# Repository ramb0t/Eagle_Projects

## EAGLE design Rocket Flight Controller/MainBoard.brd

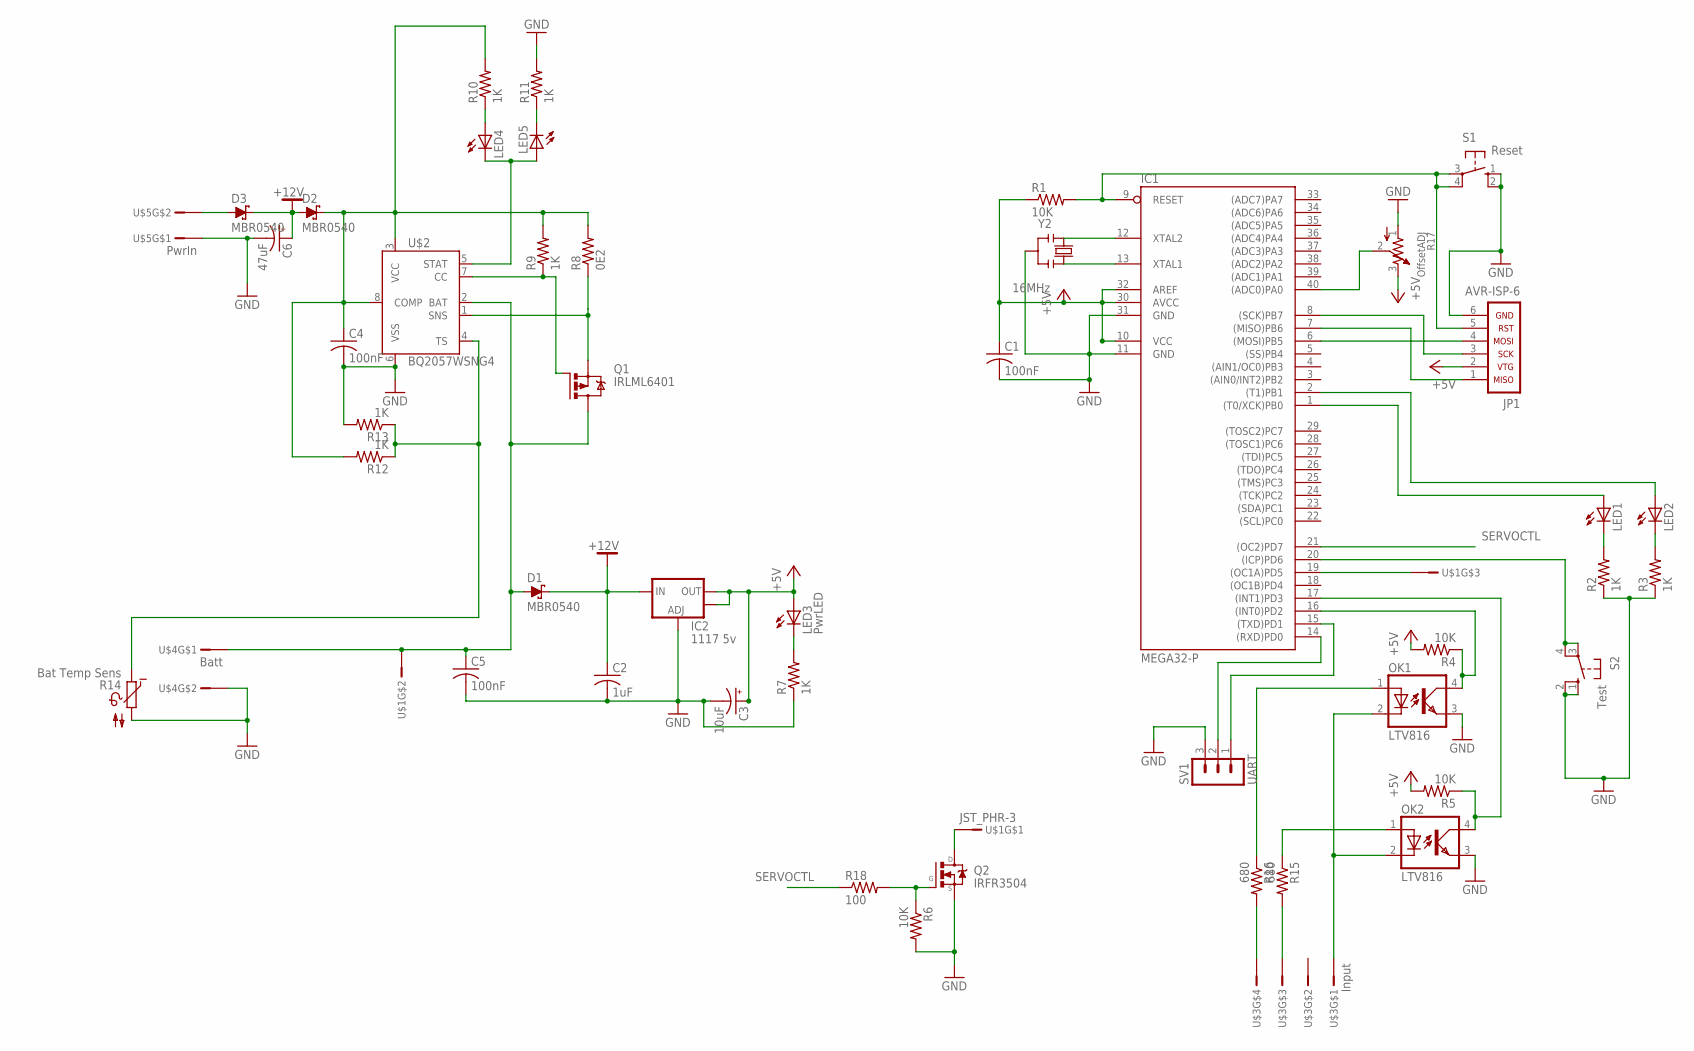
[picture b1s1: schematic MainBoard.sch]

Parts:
C1, C4, C5: 100nF; C0805K
C2: 1uF; C0805K
C3: 10uF; E2,5-7
C6: 47uF; E2,5-7
D1, D2, D3: MBR0540; SOD123
IC1: MEGA32-P; DIL40
IC2: 1117 5v; SOT223
JP1: AVR-ISP-6
LED1, LED2, LED4, LED5: LED3MM
LED3: PwrLED; LED3MM
OK1, OK2: LTV816; DIL04
Q1: IRLML6401; MICRO3
Q2: IRFR3504; DPAK
R1, R4, R5, R6: 10K; R0805
R2, R3, R7, R9, R10, R11, R12, R13: 1K; R0805
R8: 0E2; M1206
R14: Bat Temp Sens; P640
R15, R16: 680; R0805
R17: OffsetADJ; 3362P
R18: 100; R0805
S1: Reset; B3F-10XX
S2: Test; B3F-10XX
SV1: UART; MA03-1
U$1: JST_PHR-3; PHR-3
U$2: BQ2057WSNG4; D_R-PDSO-G8
U$3: Input; PHR-4
U$4: Batt; PHR-2
U$5: PwrIn; PHR-2
Y2: 16MHz; RESONATOR

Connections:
+5V: C1.1, C3.+, IC1.10 (VCC), IC1.30 (AVCC), IC1.32 (AREF), IC2.2 (OUT), IC2.4 (OUT), JP1.2, LED3.A, R1.1, R4.2, R5.2, R17.3
+12V: C2.1, C6.+, D1.C, D2.A, D3.C, IC2.3 (IN)
GND: C1.2, C2.2, C3.-, C4.2, C5.2, C6.-, IC1.11 (GND), IC1.31 (GND), IC2.1 (ADJ), JP1.6, OK1.3 (EMIT), OK2.3 (EMIT), Q2.3 (S), R2.1, R3.1, R6.2, R7.1, R11.2, R13.2, R14.2, R17.1, S1.1 (S), S1.2 (S1), S2.1 (S), S2.2 (S1), SV1.3, U$2.6 (VSS), U$4.P$2, U$5.P$1, Y2.2
unnamed: OK1.2 (C), OK2.2 (C), U$3.P$1
unnamed: IC1.9 (RESET), JP1.5, R1.2, S1.3, S1.4 (P1)
unnamed: IC1.8 ((SCK)PB7), JP1.3
unnamed: IC1.6 ((MOSI)PB5), JP1.4
unnamed: IC1.7 ((MISO)PB6), JP1.1
unnamed: D3.A, U$5.P$2
unnamed: IC1.15 ((TXD)PD1), SV1.1
unnamed: LED4.K (C), LED5.A, U$2.5 (STAT)
unnamed: IC1.13 (XTAL1), Y2.3
unnamed: IC1.12 (XTAL2), Y2.1
unnamed: IC1.19 ((OC1A)PD5), U$1.P$3
unnamed: LED1.K (C), R2.2
unnamed: LED2.K (C), R3.2
unnamed: IC1.14 ((RXD)PD0), SV1.2
unnamed: IC1.1 ((T0/XCK)PB0), LED1.A
unnamed: IC1.40 ((ADC0)PA0), R17.2
unnamed: IC1.2 ((T1)PB1), LED2.A
unnamed: LED3.K (C), R7.2
unnamed: IC1.20 ((ICP)PD6), S2.3, S2.4 (P1)
unnamed: C5.1, D1.A, Q1.3 (D), U$1.P$2, U$2.2 (BAT), U$4.P$1
unnamed: Q2.1 (G), R6.1, R18.2
unnamed: Q2.4 (D), U$1.P$1
unnamed: Q1.2 (S), R8.1, U$2.1 (SNS)
unnamed: Q1.1 (G), R9.1, U$2.7 (CC)
unnamed: LED5.K (C), R11.1
unnamed: LED4.A, R10.1
unnamed: R12.1, R13.1, R14.1, U$2.4 (TS)
unnamed: R16.2, U$3.P$4
unnamed: C4.1, D2.C, R8.2, R9.2, R10.2, R12.2, U$2.3 (VCC), U$2.8 (COMP)
unnamed: IC1.17 ((INT1)PD3), OK2.4 (COL), R5.1
unnamed: IC1.16 ((INT0)PD2), OK1.4 (COL), R4.1
unnamed: R15.2, U$3.P$3
unnamed: OK1.1 (A), R16.1
unnamed: OK2.1 (A), R15.1
SERVOCTL: IC1.21 ((OC2)PD7), R18.1

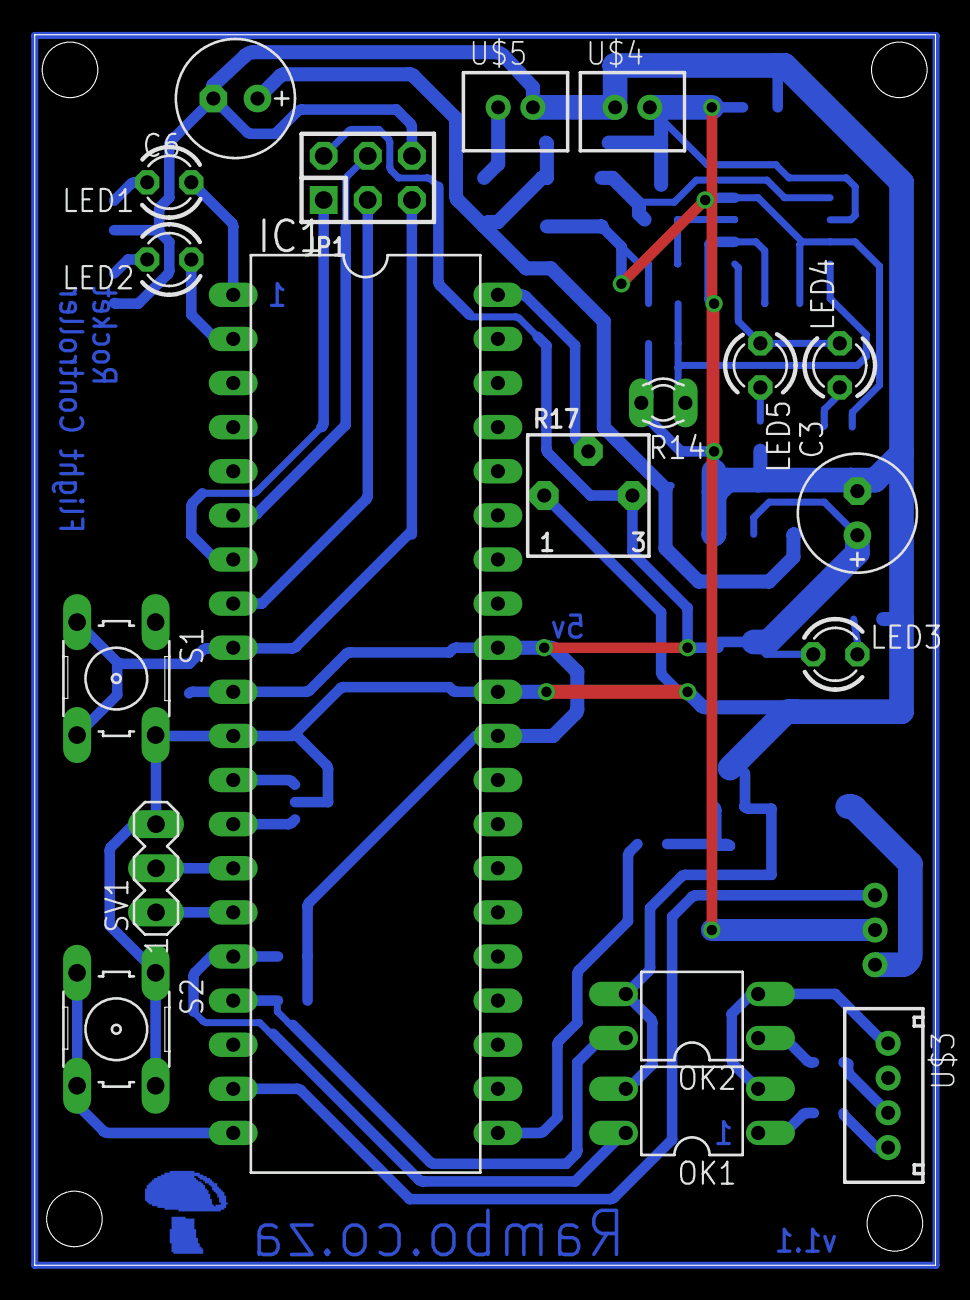
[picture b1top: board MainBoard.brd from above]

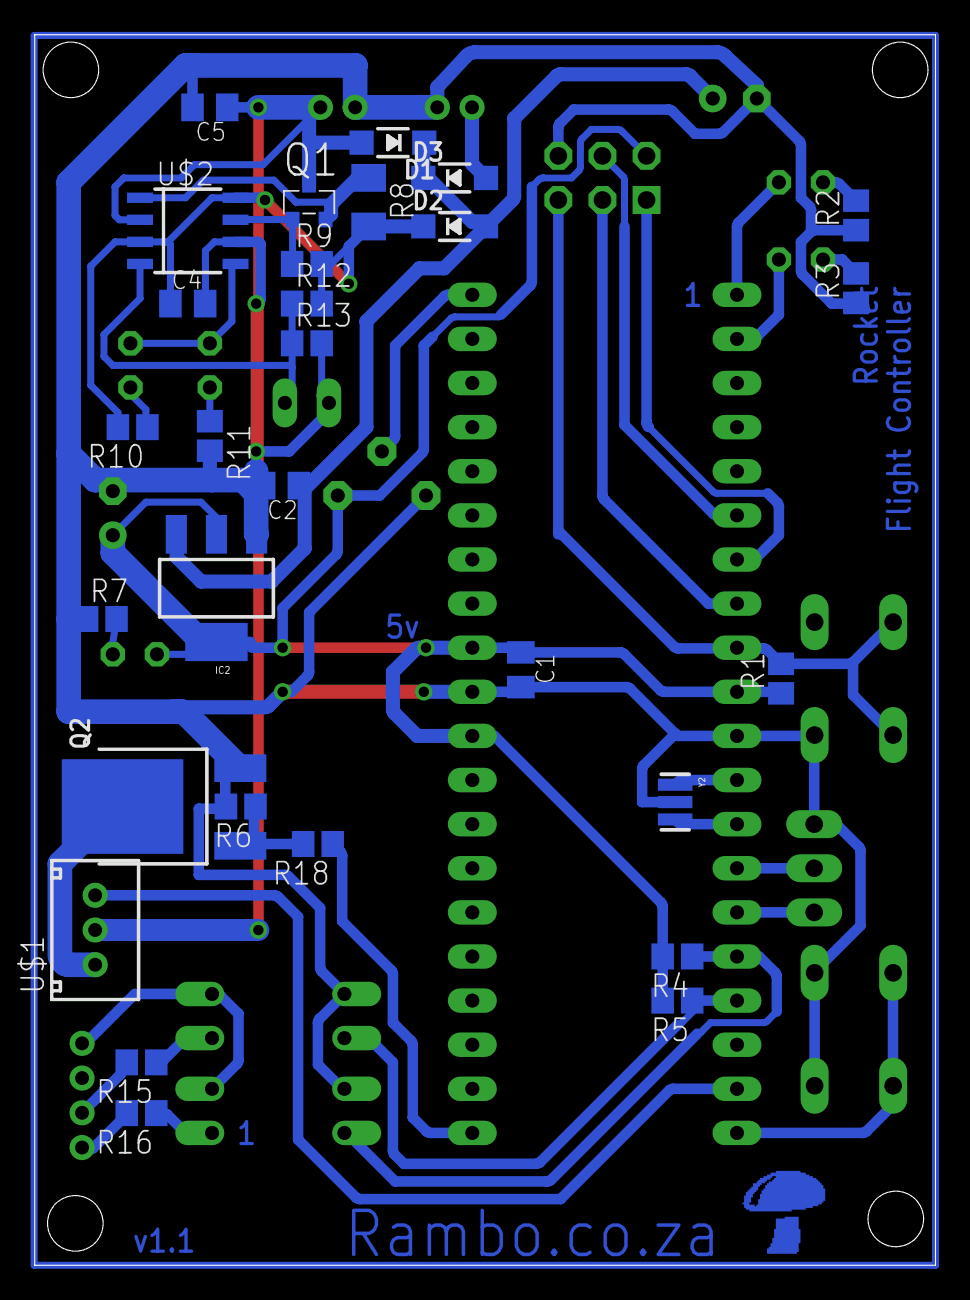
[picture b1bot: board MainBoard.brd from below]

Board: 2 copper layers, 51.9 x 70.9 mm, 48 parts (29 on the bottom side), 38 nets.

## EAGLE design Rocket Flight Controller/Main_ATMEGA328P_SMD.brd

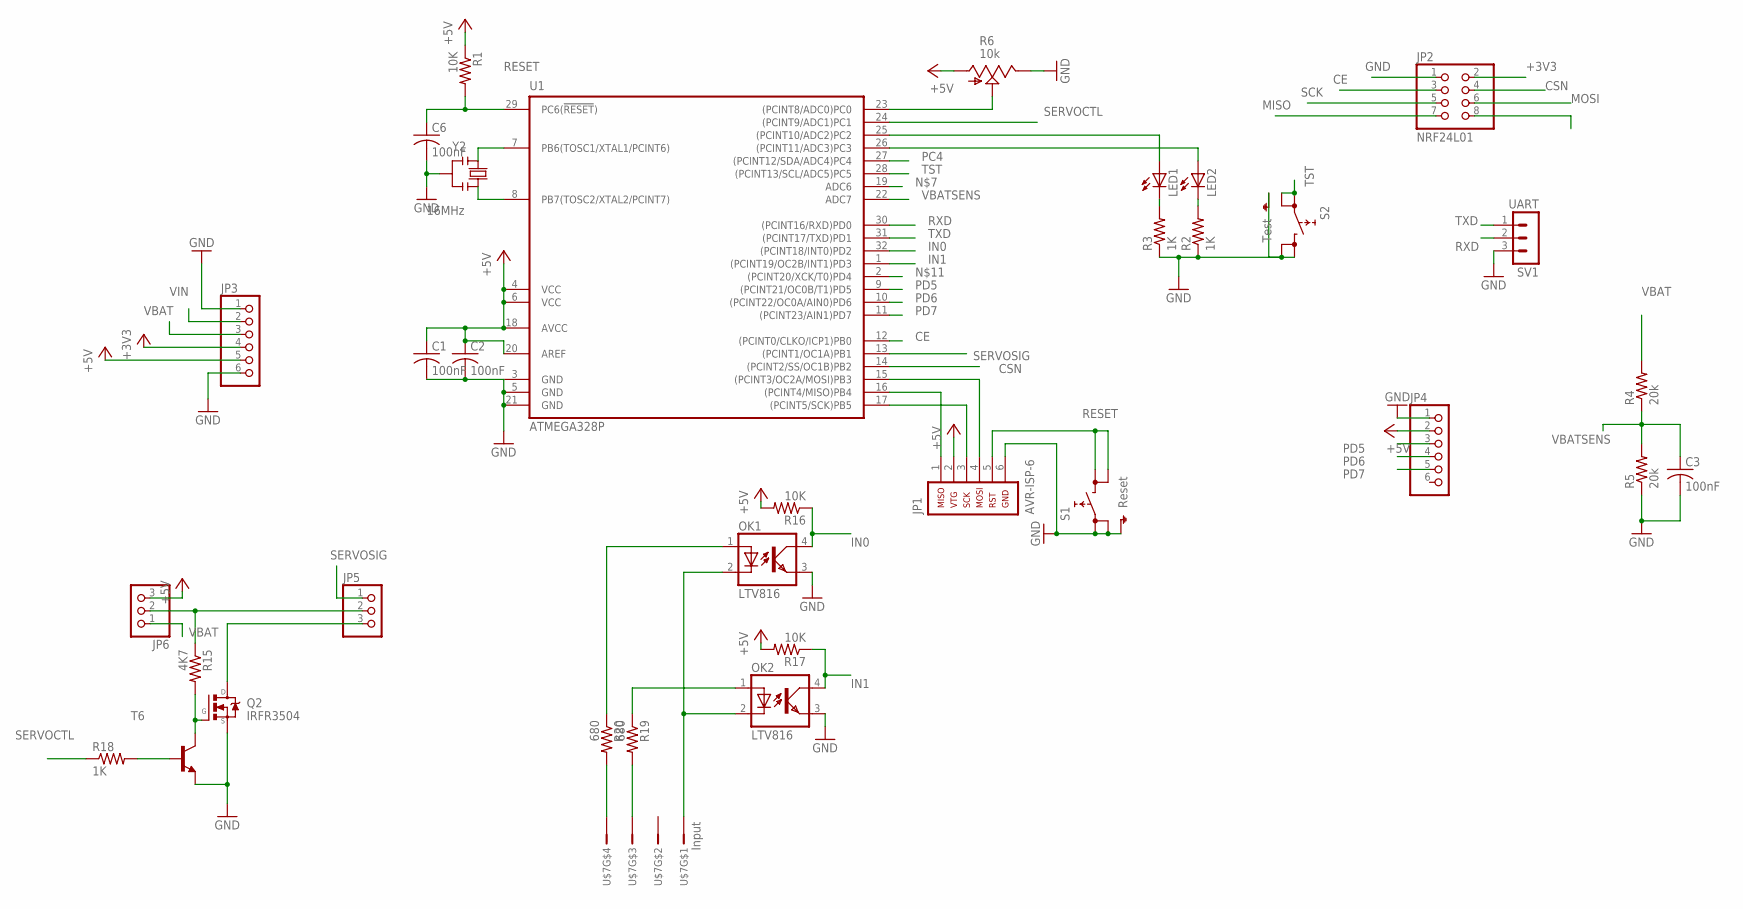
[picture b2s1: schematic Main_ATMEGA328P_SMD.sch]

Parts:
C1, C2, C3, C6: 100nF; C0805K
JP1: AVR-ISP-6
JP2: NRF24L01; 2X04
JP3, JP4: PINHD-1X6; 1X06
JP5, JP6: PINHD-1X3; 1X03
LED1, LED2: LEDCHIPLED_0805; CHIPLED_0805
OK1, OK2: LTV816; DIL04
Q2: IRFR3504; DPAK
R1, R16, R17: 10K; R0805
R2, R3, R18: 1K; R0805
R4, R5: 20k; R0805
R6: 10k; CT6
R15: 4K7; R0805
R19, R20: 680; R0805
S1: Reset; SKHMPXE010
S2: Test; SKHMPXE010
SV1: UART; MA03-1
T6: MMBT2222ALT1-NPN-SOT23-BEC; SOT23-BEC
U1: ATMEGA328P; TQFP32A
U$7: Input; PHR-4
Y2: 16MHz; RESONATOR

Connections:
+3V3: JP2.2, JP3.4
+5V: C1.1, C2.1, JP1.2, JP3.5, JP4.2, JP6.3, R1.1, R6.A, R16.2, R17.2, U1.4 (VCC), U1.6 (VCC), U1.18 (AVCC), U1.20 (AREF)
CE: JP2.3, U1.12 ((PCINT0/CLKO/ICP1)PB0)
CSN: JP2.4, U1.14 ((PCINT2/SS/OC1B)PB2)
GND: C1.2, C2.2, C3.2, C6.2, JP1.6, JP2.1, JP3.1, JP3.6, JP4.1, OK1.3 (EMIT), OK2.3 (EMIT), Q2.3 (S), R2.1, R3.1, R5.1, R6.E, S1.1 (1.1), S1.2 (1.2), S1.5 (SH), S2.3 (2.1), S2.4 (2.2), S2.5 (SH), SV1.3, T6.E, U1.3 (GND), U1.5 (GND), U1.21 (GND), Y2.2
IN0: OK1.4 (COL), R16.1, U1.32 ((PCINT18/INT0)PD2)
IN1: OK2.4 (COL), R17.1, U1.1 ((PCINT19/OC2B/INT1)PD3)
MISO: JP1.1, JP2.7, U1.16 ((PCINT4/MISO)PB4)
MOSI: JP1.4, JP2.6, U1.15 ((PCINT3/OC2A/MOSI)PB3)
unnamed: Q2.1 (G), R15.2, T6.C
unnamed: R6.S, U1.23 ((PCINT8/ADC0)PC0)
unnamed: LED1.A, U1.25 ((PCINT10/ADC2)PC2)
unnamed: LED2.A, U1.26 ((PCINT11/ADC3)PC3)
unnamed: R18.2, T6.B
unnamed: U1.8 (PB7(TOSC2/XTAL2/PCINT7)), Y2.3
unnamed: U1.7 (PB6(TOSC1/XTAL1/PCINT6)), Y2.1
unnamed: LED2.C, R2.2
unnamed: LED1.C, R3.2
unnamed: JP5.2, JP6.2, R15.1
unnamed: JP5.3, Q2.4 (D)
unnamed: OK1.2 (C), OK2.2 (C), U$7.P$1
unnamed: R20.2, U$7.P$4
unnamed: R19.2, U$7.P$3
unnamed: OK1.1 (A), R20.1
unnamed: OK2.1 (A), R19.1
PC4: U1.27 ((PCINT12/SDA/ADC4)PC4)
PD5: JP4.3, U1.9 ((PCINT21/OC0B/T1)PD5)
PD6: JP4.4, U1.10 ((PCINT22/OC0A/AIN0)PD6)
PD7: JP4.5, U1.11 ((PCINT23/AIN1)PD7)
RESET: C6.1, JP1.5, R1.2, S1.3 (2.1), S1.4 (2.2), U1.29 (PC6(!RESET!))
RXD: SV1.2, U1.30 ((PCINT16/RXD)PD0)
SCK: JP1.3, JP2.5, U1.17 ((PCINT5/SCK)PB5)
SERVOCTL: R18.1, U1.24 ((PCINT9/ADC1)PC1)
SERVOSIG: JP5.1, U1.13 ((PCINT1/OC1A)PB1)
TST: S2.1 (1.1), S2.2 (1.2), U1.28 ((PCINT13/SCL/ADC5)PC5)
TXD: SV1.1, U1.31 ((PCINT17/TXD)PD1)
VBAT: JP3.3, JP6.1, R4.2
VBATSENS: C3.1, R4.1, R5.2, U1.22 (ADC7)
VIN: JP3.2

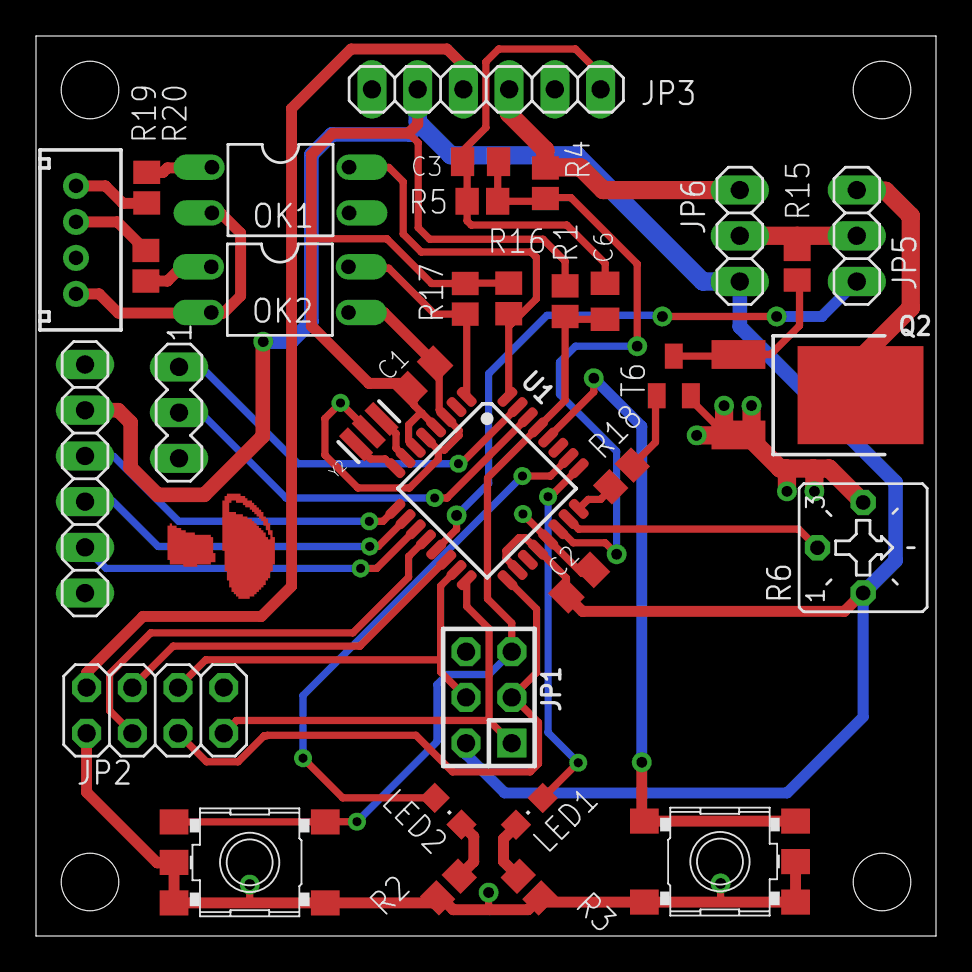
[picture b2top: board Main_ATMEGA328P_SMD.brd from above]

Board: 2 copper layers, 50.0 x 50.0 mm, 34 parts (0 on the bottom side), 37 nets.

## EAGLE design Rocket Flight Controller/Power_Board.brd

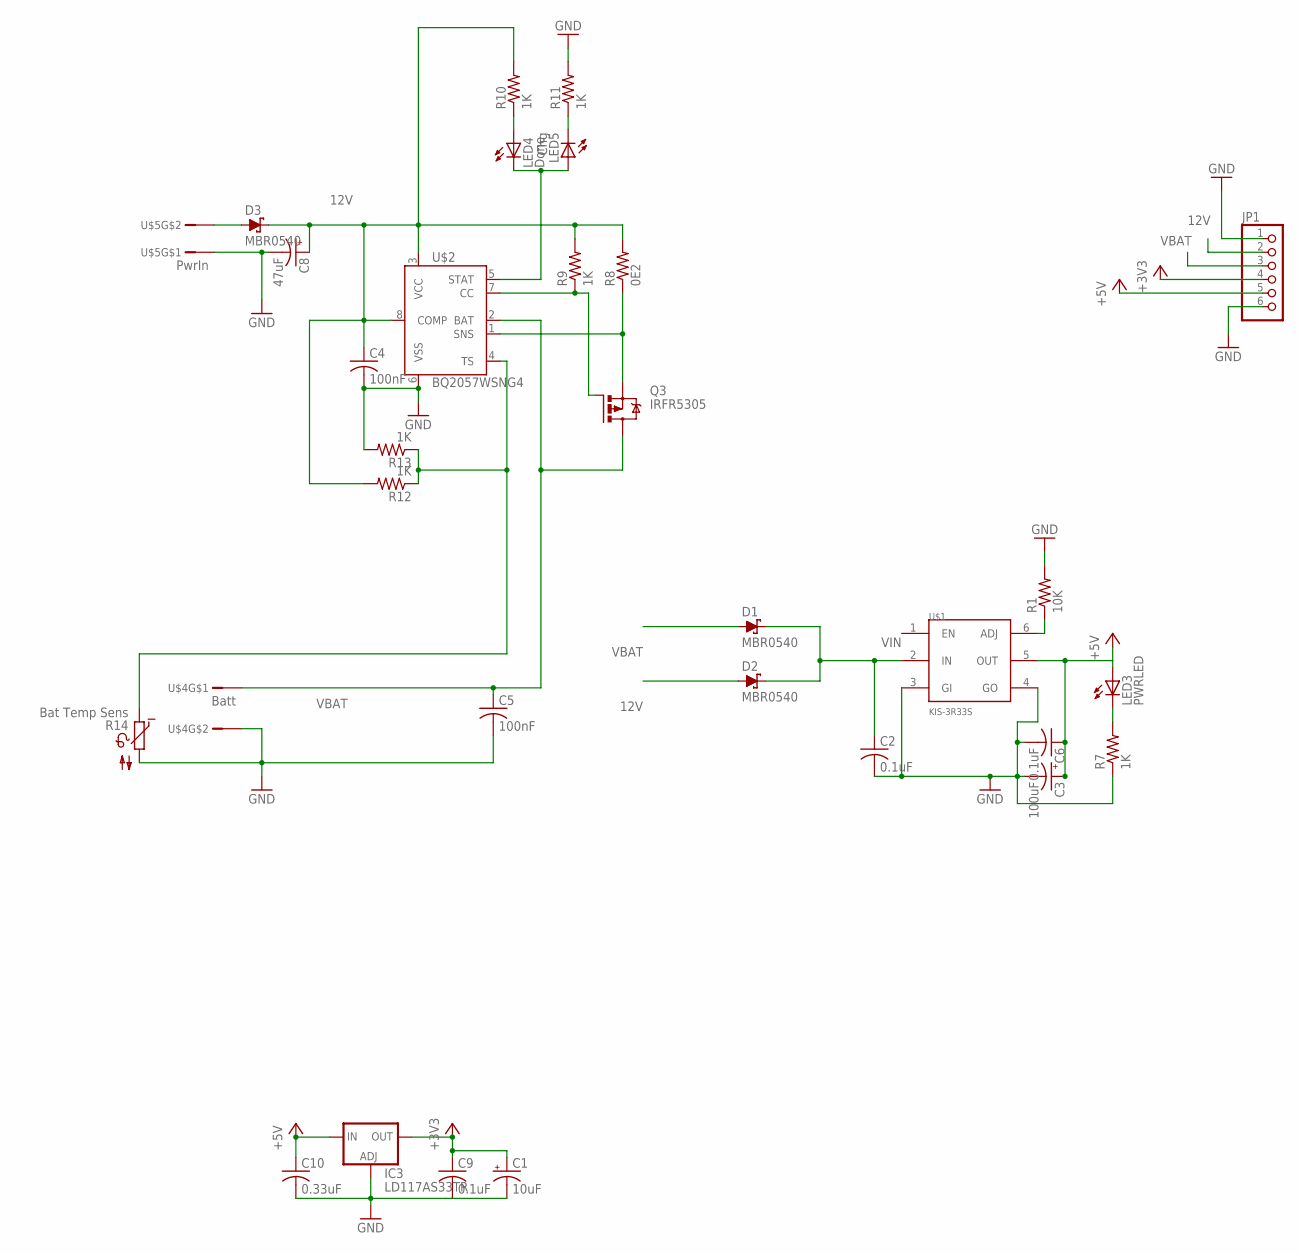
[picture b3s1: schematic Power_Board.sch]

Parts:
C1: 10uF; E2,5-7
C2, C6, C9: 0.1uF; C0805K
C3: 100uF; E2,5-7
C4, C5: 100nF; C0805K
C8: 47uF; E2,5-7
C10: 0.33uF; C0805K
D1, D2, D3: MBR0540; SOD123
IC3: LD117AS33TR; SOT223
JP1: PINHD-1X6; 1X06
LED3: PWRLED; CHIPLED_0805
LED4: Done; CHIPLED_0805
LED5: Chg; CHIPLED_0805
Q3: IRFR5305; D-PAK_TO252AA
R1: 10K; R0805
R7, R9, R10, R11, R12, R13: 1K; R0805
R8: 0E2; M1206
R14: Bat Temp Sens; P640
U$1: KIS-3R33S
U$2: BQ2057WSNG4; D_R-PDSO-G8
U$4: Batt; PHR-2
U$5: PwrIn; PHR-2

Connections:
12V: C4.1, C8.+, D2.A, D3.C, JP1.2, R8.2, R9.2, R10.2, R12.2, U$2.3 (VCC), U$2.8 (COMP)
+3V3: C1.+, C9.1, IC3.4 (OUT), JP1.4
+5V: C3.+, C6.1, C10.1, IC3.3 (IN), JP1.5, LED3.A, U$1.5 (OUT)
GND: C1.-, C2.2, C3.-, C4.2, C5.2, C6.2, C8.-, C9.2, C10.2, IC3.1 (ADJ), JP1.1, JP1.6, R1.2, R7.1, R11.2, R13.2, R14.2, U$1.3 (GI), U$1.4 (GO), U$2.6 (VSS), U$4.P$2, U$5.P$1
unnamed: R1.1, U$1.6 (ADJ)
unnamed: LED3.C, R7.2
unnamed: LED4.C, LED5.A, U$2.5 (STAT)
unnamed: LED4.A, R10.1
unnamed: D3.A, U$5.P$2
unnamed: Q3.3 (S), R8.1, U$2.1 (SNS)
unnamed: Q3.1 (G), R9.1, U$2.7 (CC)
unnamed: LED5.C, R11.1
unnamed: R12.1, R13.1, R14.1, U$2.4 (TS)
VBAT: C5.1, D1.A, JP1.3, Q3.4 (D), U$2.2 (BAT), U$4.P$1
VIN: C2.1, D1.C, D2.C, U$1.2 (IN)

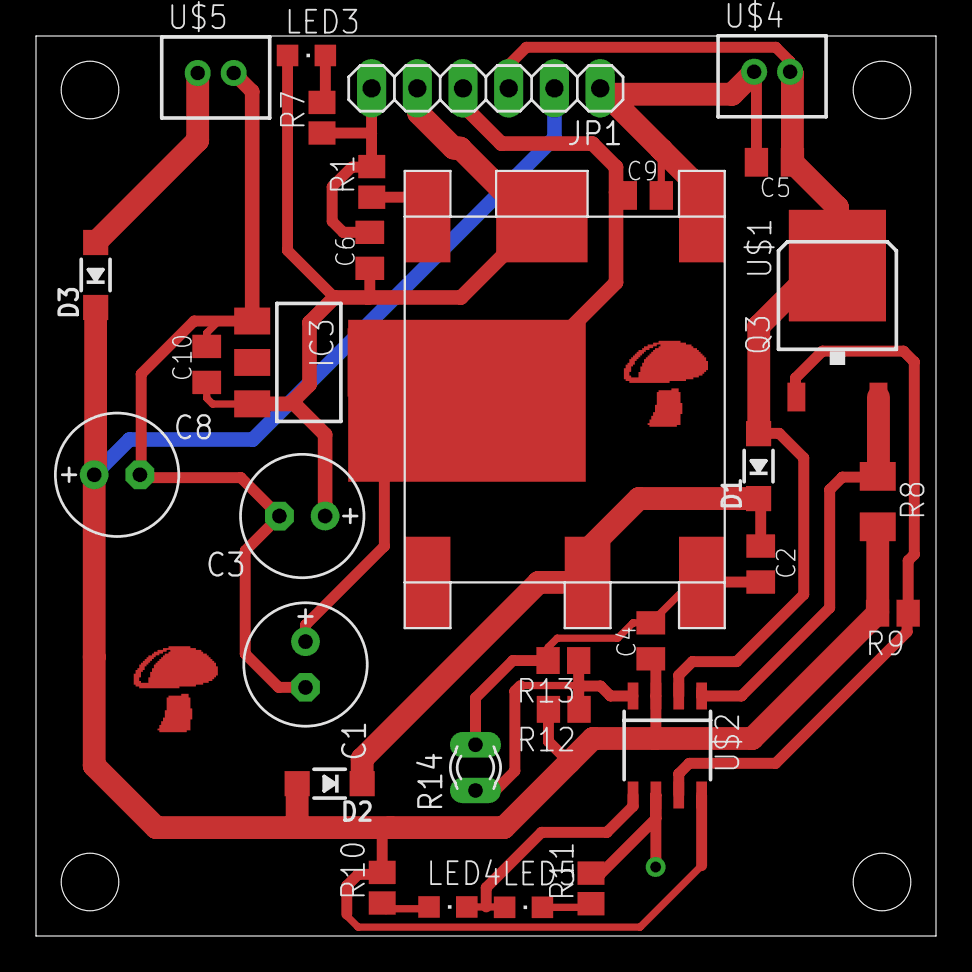
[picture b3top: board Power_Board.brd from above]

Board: 2 copper layers, 50.0 x 50.0 mm, 31 parts (0 on the bottom side), 15 nets.

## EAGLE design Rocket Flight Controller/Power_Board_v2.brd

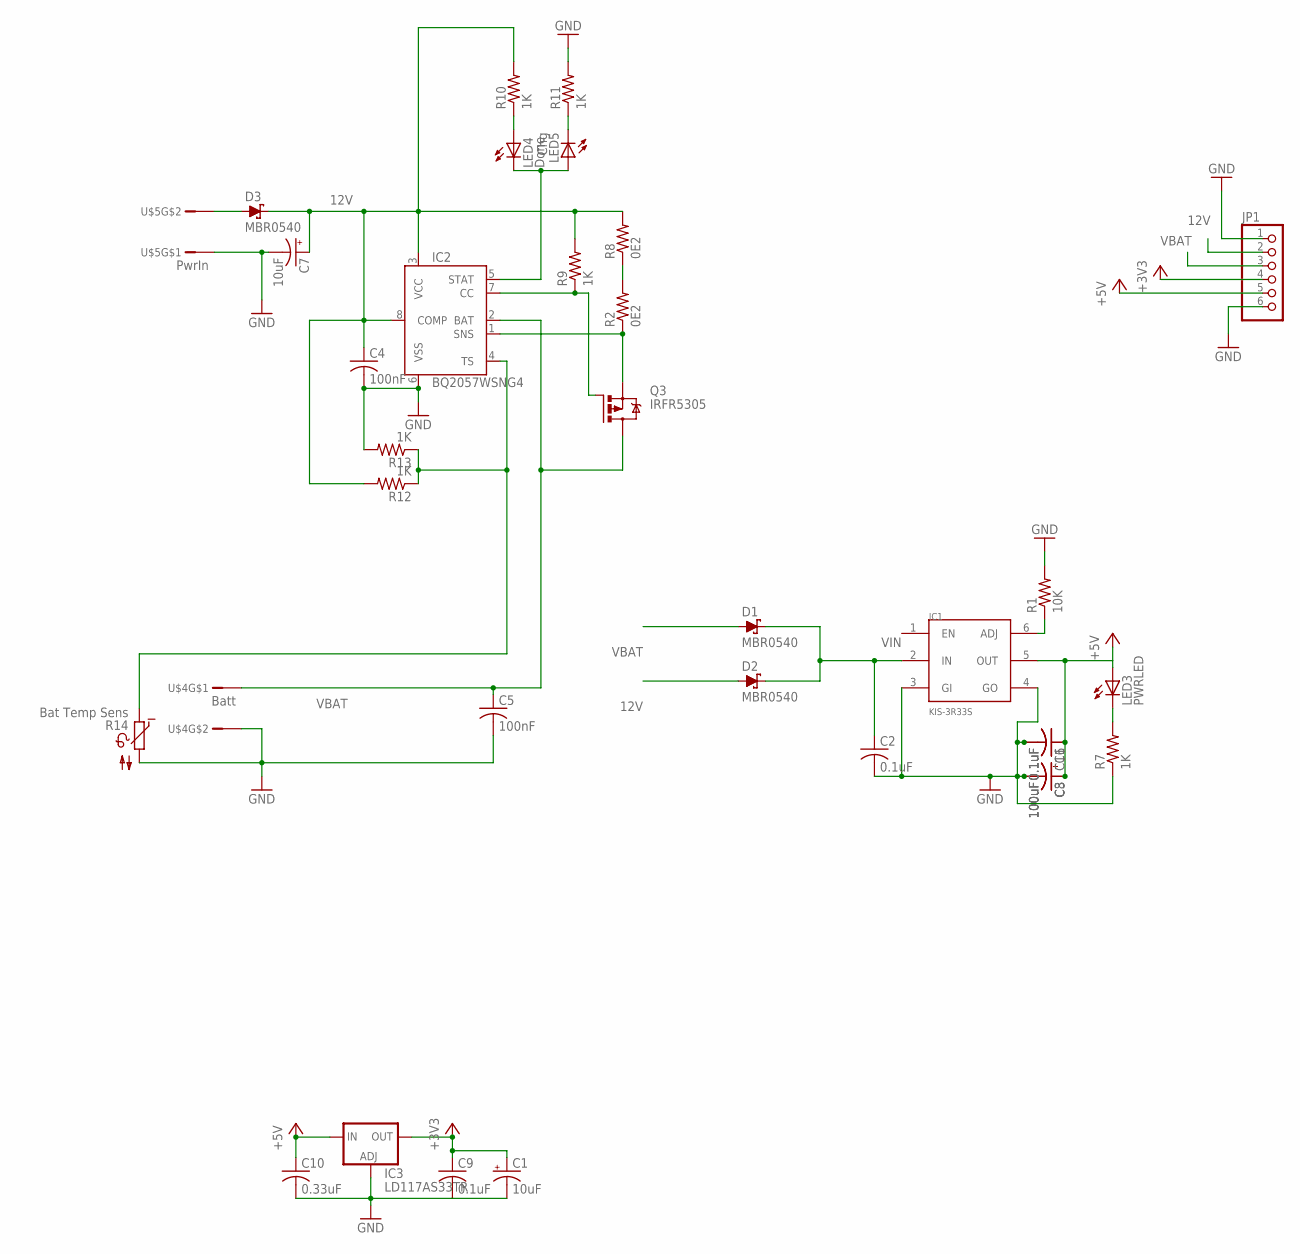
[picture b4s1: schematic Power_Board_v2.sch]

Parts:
C1, C7: 10uF; 153CLV-0405
C2, C6, C9, C11: 0.1uF; C0805K
C3, C8: 100uF; PANASONIC_D
C4, C5: 100nF; C0805K
C10: 0.33uF; C0805K
D1, D2, D3: MBR0540; SOD123
IC1: KIS-3R33S
IC2: BQ2057WSNG4; D_R-PDSO-G8
IC3: LD117AS33TR; SOT223
JP1: PINHD-1X6; 1X06
LED3: PWRLED; CHIPLED_0805
LED4: Done; CHIPLED_0805
LED5: Chg; CHIPLED_0805
Q3: IRFR5305; D-PAK_TO252AA
R1: 10K; R0805
R2, R8: 0E2; M1206
R7, R9, R10, R11, R12, R13: 1K; R0805
R14: Bat Temp Sens; P640
U$4: Batt; PHR-2
U$5: PwrIn; PHR-2

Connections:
12V: C4.1, C7.+, D2.A, D3.C, IC2.3 (VCC), IC2.8 (COMP), JP1.2, R8.2, R9.2, R10.2, R12.2
+3V3: C1.+, C9.1, IC3.4 (OUT), JP1.4
+5V: C3.+, C6.1, C8.+, C10.1, C11.1, IC1.5 (OUT), IC3.3 (IN), JP1.5, LED3.A
GND: C1.-, C2.2, C3.-, C4.2, C5.2, C6.2, C7.-, C8.-, C9.2, C10.2, C11.2, IC1.3 (GI), IC1.4 (GO), IC2.6 (VSS), IC3.1 (ADJ), JP1.1, JP1.6, R1.2, R7.1, R11.2, R13.2, R14.2, U$4.P$2, U$5.P$1
unnamed: R2.2, R8.1
unnamed: IC1.6 (ADJ), R1.1
unnamed: LED3.C, R7.2
unnamed: IC2.5 (STAT), LED4.C, LED5.A
unnamed: LED4.A, R10.1
unnamed: D3.A, U$5.P$2
unnamed: IC2.1 (SNS), Q3.3 (S), R2.1
unnamed: IC2.7 (CC), Q3.1 (G), R9.1
unnamed: LED5.C, R11.1
unnamed: IC2.4 (TS), R12.1, R13.1, R14.1
VBAT: C5.1, D1.A, IC2.2 (BAT), JP1.3, Q3.4 (D), U$4.P$1
VIN: C2.1, D1.C, D2.C, IC1.2 (IN)

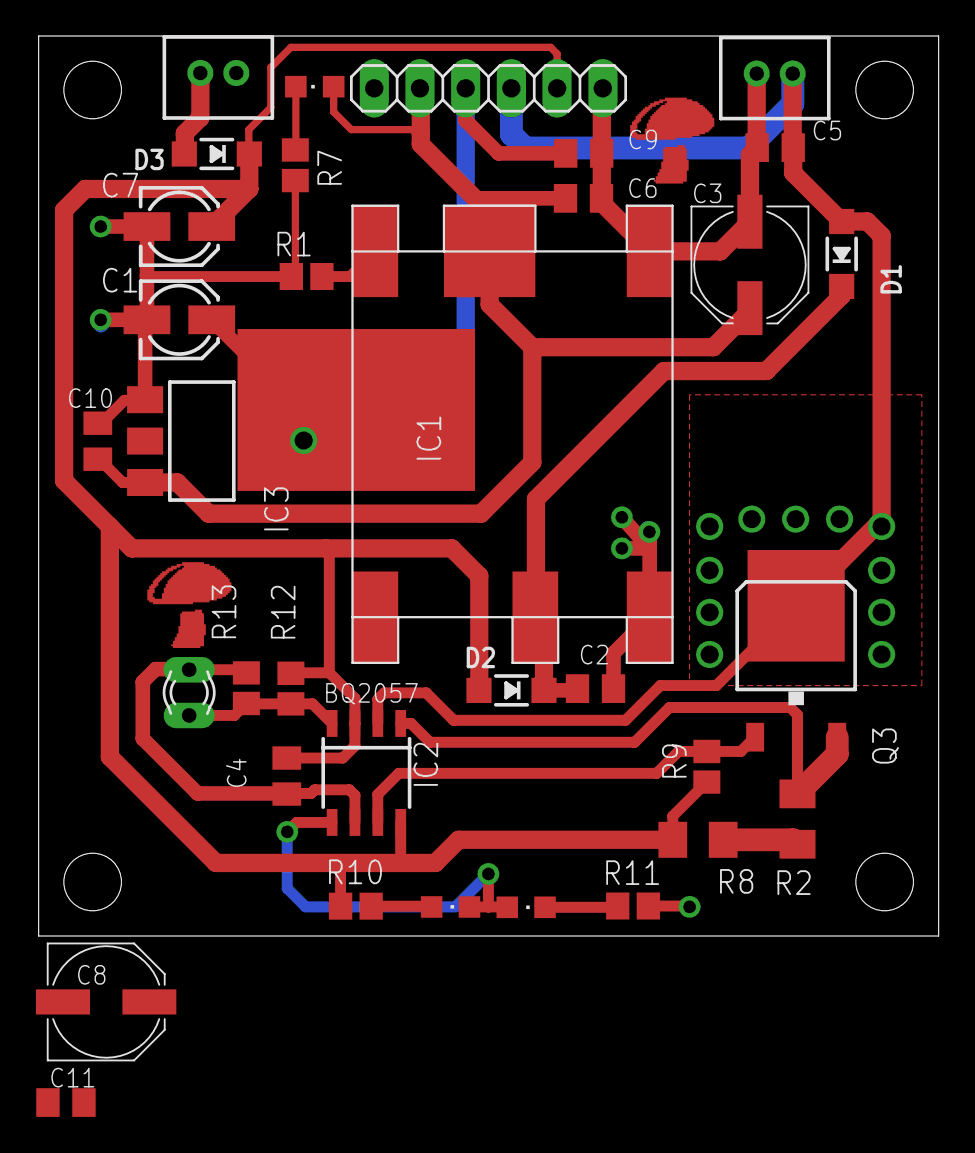
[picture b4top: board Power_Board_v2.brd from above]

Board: 2 copper layers, 50.0 x 50.0 mm, 34 parts (0 on the bottom side), 16 nets.

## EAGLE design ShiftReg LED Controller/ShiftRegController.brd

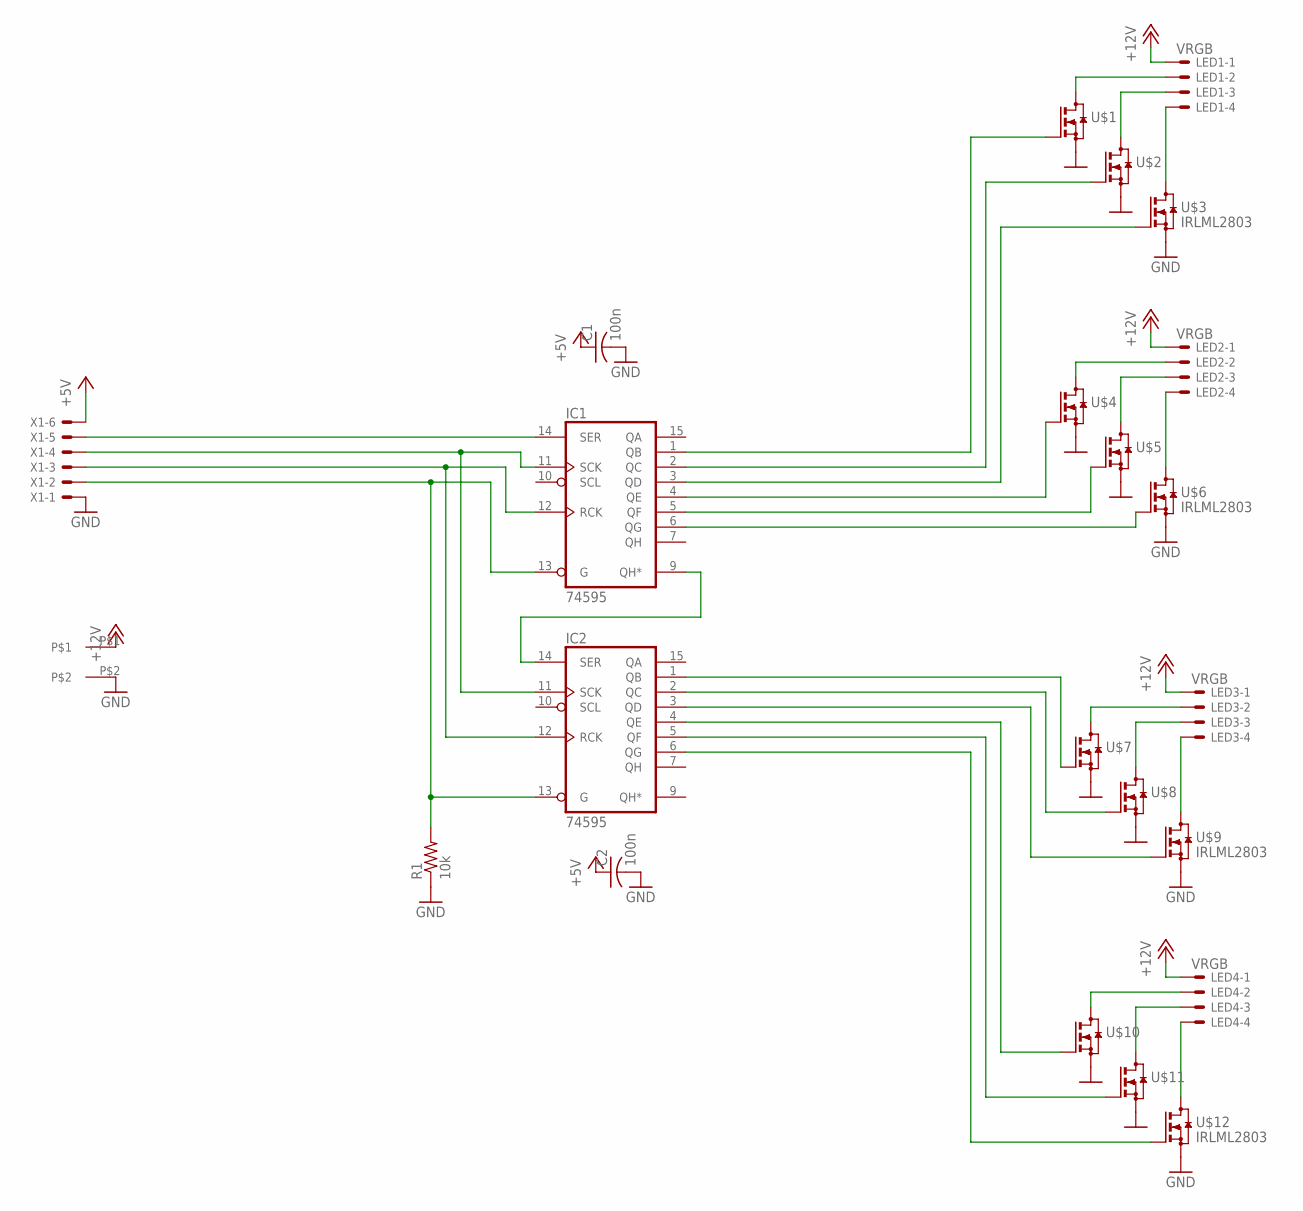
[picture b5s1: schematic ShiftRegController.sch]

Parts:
C1, C2: 100n; C0805
IC1, IC2: 74595; TSSOP16
LED1, LED2, LED3, LED4: VRGB; 22-23-2041
R1: 10k; R0805
U$1, U$2, U$3, U$4, U$5, U$6, U$7, U$8, U$9, U$10, U$11, U$12: IRLML2803; SOT23
U$13: DG301-5.0
X1: 22-23-2061

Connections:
+5V: C1.1, C2.1
+12V: LED1.1, LED2.1, LED3.1, LED4.1, U$13.P$1
GND: C1.2, C2.2, IC1.8 (GND), IC2.8 (GND), R1.1, U$1.2 (S), U$2.2 (S), U$3.2 (S), U$4.2 (S), U$5.2 (S), U$6.2 (S), U$7.2 (S), U$8.2 (S), U$9.2 (S), U$10.2 (S), U$11.2 (S), U$12.2 (S), U$13.P$2, X1.1
unnamed: IC1.9 (QH*), IC2.14 (SER)
unnamed: LED2.2, U$4.3 (D)
unnamed: LED1.2, U$1.3 (D)
unnamed: LED1.3, U$2.3 (D)
unnamed: LED1.4, U$3.3 (D)
unnamed: LED2.3, U$5.3 (D)
unnamed: LED2.4, U$6.3 (D)
unnamed: LED3.2, U$7.3 (D)
unnamed: LED3.3, U$8.3 (D)
unnamed: LED3.4, U$9.3 (D)
unnamed: LED4.2, U$10.3 (D)
unnamed: LED4.3, U$11.3 (D)
unnamed: LED4.4, U$12.3 (D)
unnamed: IC2.1 (QB), U$7.1 (G)
unnamed: IC1.1 (QB), U$1.1 (G)
unnamed: IC1.2 (QC), U$2.1 (G)
unnamed: IC1.3 (QD), U$3.1 (G)
unnamed: IC1.6 (QG), U$6.1 (G)
unnamed: IC1.5 (QF), U$5.1 (G)
unnamed: IC1.4 (QE), U$4.1 (G)
unnamed: IC2.2 (QC), U$8.1 (G)
unnamed: IC2.3 (QD), U$9.1 (G)
unnamed: IC2.4 (QE), U$10.1 (G)
unnamed: IC2.5 (QF), U$11.1 (G)
unnamed: IC2.6 (QG), U$12.1 (G)
unnamed: IC1.14 (SER), X1.5
unnamed: IC1.11 (SCK), IC2.11 (SCK), X1.4
unnamed: IC1.12 (RCK), IC2.12 (RCK), X1.3
unnamed: IC1.13 (G), IC2.13 (G), R1.2, X1.2
VCC: IC1.16 (VCC), IC2.16 (VCC), X1.6

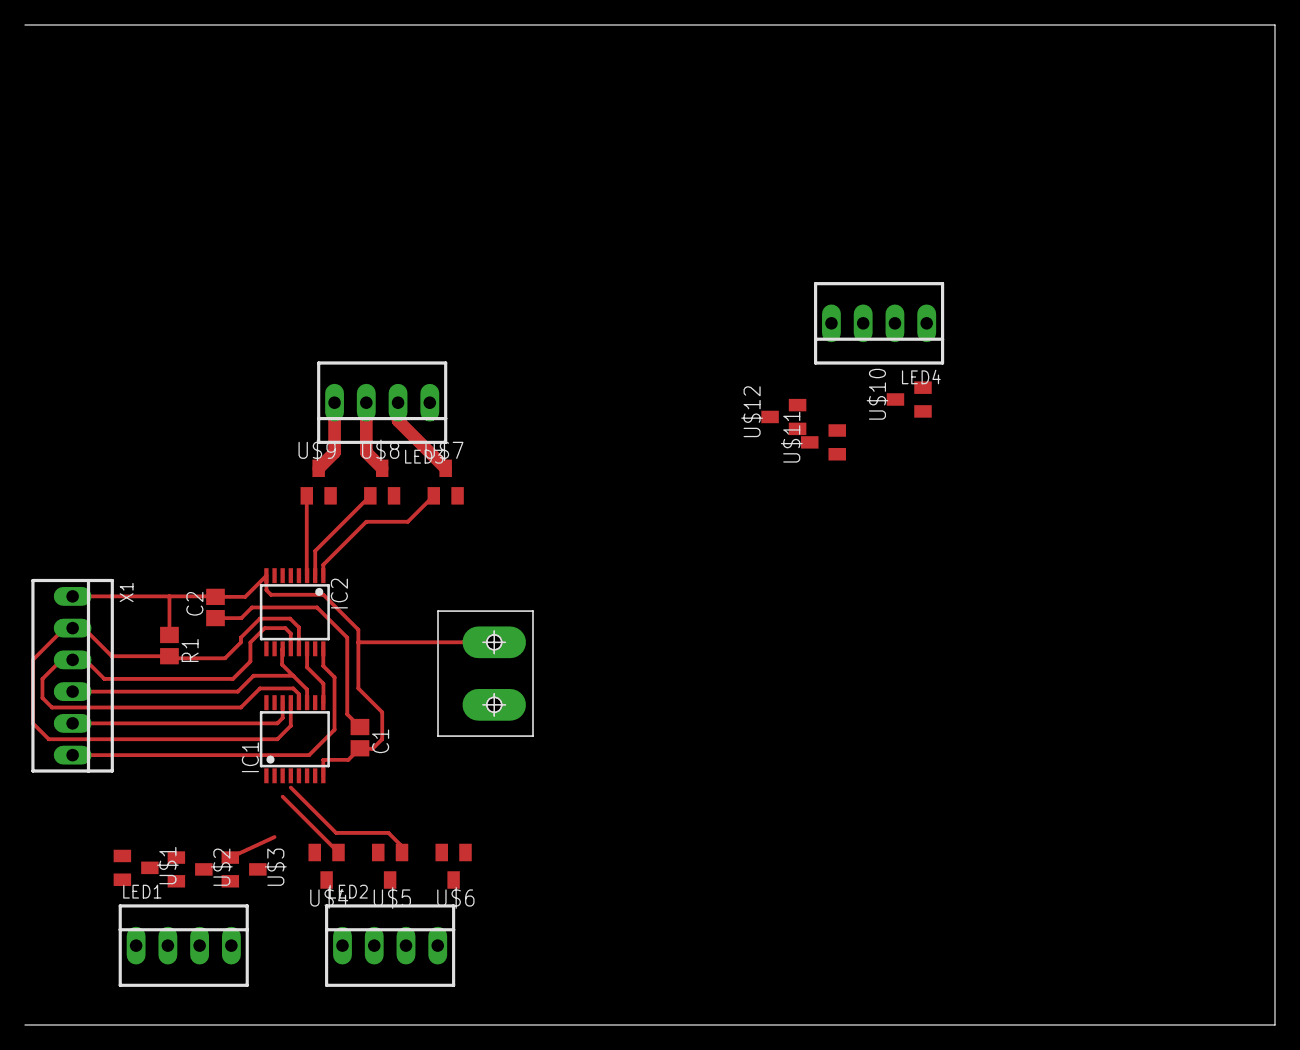
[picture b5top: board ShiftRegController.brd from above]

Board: 2 copper layers, 100.0 x 80.0 mm, 23 parts (0 on the bottom side), 33 nets.

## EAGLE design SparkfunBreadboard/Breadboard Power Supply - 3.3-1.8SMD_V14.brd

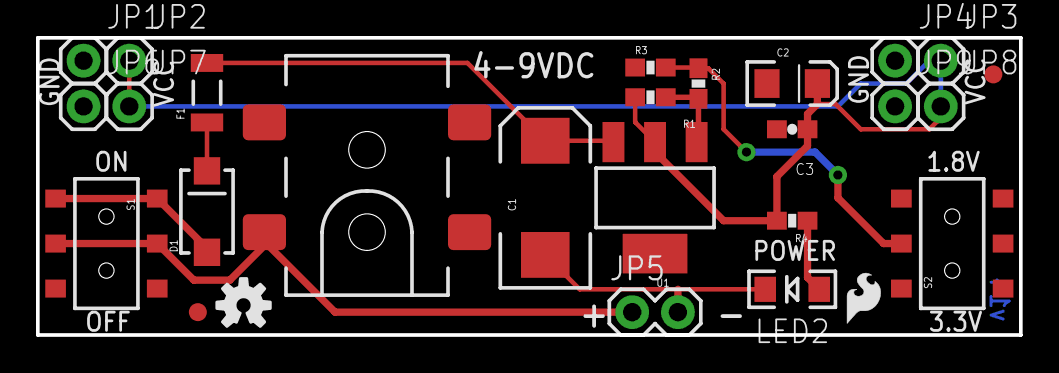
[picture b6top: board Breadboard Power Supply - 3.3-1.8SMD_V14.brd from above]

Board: 2 copper layers, 54.6 x 16.5 mm, 29 parts (1 on the bottom side), 9 nets.

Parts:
C1: 100uF; EIA7343
C2: 10uF; EIA3216
C3: 0.1uF; 0603-CAP
D1: 1N4001; SMA-DIODE-TYLERALT1
F1: PTCSMD-W; PTC-1206-WIDE
FRAME1: FRAME-LETTER; CREATIVE_COMMONS
J1: POWER_JACKOVERPASTE_REDBOARD_0603; POWER_JACK_SMD_OVERPASTE_REDBOARD_0603
JP1, JP2, JP3, JP4, JP6, JP7, JP8, JP9: M01PTH; 1X01
JP5: 1X02
LED2: Power; LED-1206
LOGO1: OSHW-LOGOS; OSHW-LOGO-S
R1, R4: 240; 0603-RES
R2: 105; 0603-RES
R3: 287; 0603-RES
S1: On/Off; AYZ0202
S2: Voltage; AYZ0202
U1: V_REG_317SMD; SOT223
U$1: LOGO-SFESK; SFE-LOGO-FLAME
U$2: LOGO-SFENEW; SFE-NEW-WEBLOGO
U$3, U$4: FIDUCIAL1X2; FIDUCIAL-1X2

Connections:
GND: C1.C, C2.C, C3.2, J1.GND, J1.P$4, JP1.1, JP4.1, JP5.2, JP6.1, JP9.1, LED2.C, R3.1, S2.3
unnamed: D1.C, F1.1
unnamed: D1.A, S1.1, S1.4
unnamed: R2.1, R3.2, S2.2
unnamed: R1.1, R2.2, U1.1
unnamed: LED2.A, R4.1
RAW: C1.A, F1.2, U1.3
VCC: C2.A, C3.1, JP2.1, JP3.1, JP7.1, JP8.1, R1.2, R4.2, U1.2
VIN: J1.VIN0, JP5.1, S1.2, S1.5

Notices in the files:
parts and their libraries:
SparkFun: Licensing: CC v3.0 Share-Alike You are welcome to use this library for commercial purposes.
bourns: Copyright (C) 2008, Bob Starr
supply0: Copyright (C) 2007, Bob Starr
SparkFun-Aesthetics: Released under the Creative Commons Attribution Share-Alike 3.0 License
